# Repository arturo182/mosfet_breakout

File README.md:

# 4x SOT-23 MOSFET Breadboard Breakout

This is a simple breakout board for 4 SOT-23 MOSFETS with optional pull resistors.

Fits in a breadboard.

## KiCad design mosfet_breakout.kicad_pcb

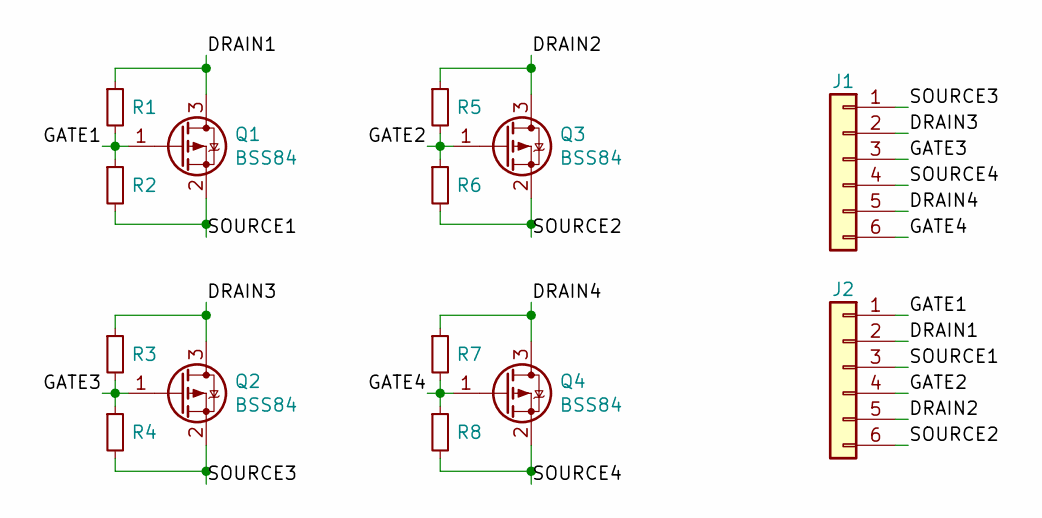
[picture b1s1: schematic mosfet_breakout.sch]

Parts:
J1, J2: Conn_01x06; PinHeader_1x06_P2.54mm_Vertical
Q1, Q2, Q3, Q4: BSS84; SOT-23
R1, R2, R3, R4, R5, R6, R7, R8: R_Small; R_0603_1608Metric

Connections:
/DRAIN1: J2.2, Q1.3 (D), R1.1
/DRAIN2: J2.5, Q3.3 (D), R5.1
/DRAIN3: J1.2, Q2.3 (D), R3.1
/DRAIN4: J1.5, Q4.3 (D), R7.1
/GATE1: J2.1, Q1.1 (G), R1.2, R2.1
/GATE2: J2.4, Q3.1 (G), R5.2, R6.1
/GATE3: J1.3, Q2.1 (G), R3.2, R4.1
/GATE4: J1.6, Q4.1 (G), R7.2, R8.1
/SOURCE1: J2.3, Q1.2 (S), R2.2
/SOURCE2: J2.6, Q3.2 (S), R6.2
/SOURCE3: J1.1, Q2.2 (S), R4.2
/SOURCE4: J1.4, Q4.2 (S), R8.2

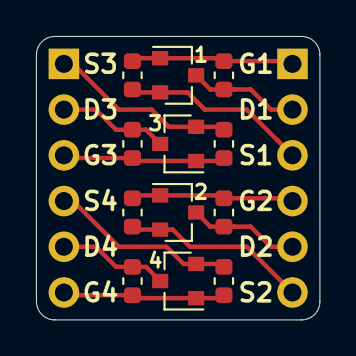
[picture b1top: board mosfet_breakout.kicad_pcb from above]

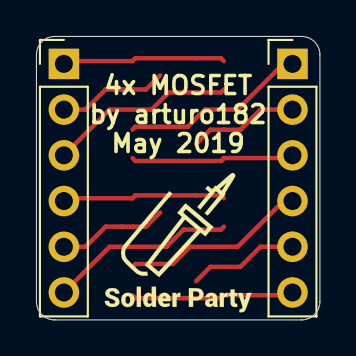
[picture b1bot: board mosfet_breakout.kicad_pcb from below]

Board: 2 copper layers, 15.7 x 15.7 mm, 14 parts (2 on the bottom side), 12 nets.

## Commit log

2019-05-30 Initial import
